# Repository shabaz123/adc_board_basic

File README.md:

# adc_board_basic
ADC board in the shape of a Pi Pico

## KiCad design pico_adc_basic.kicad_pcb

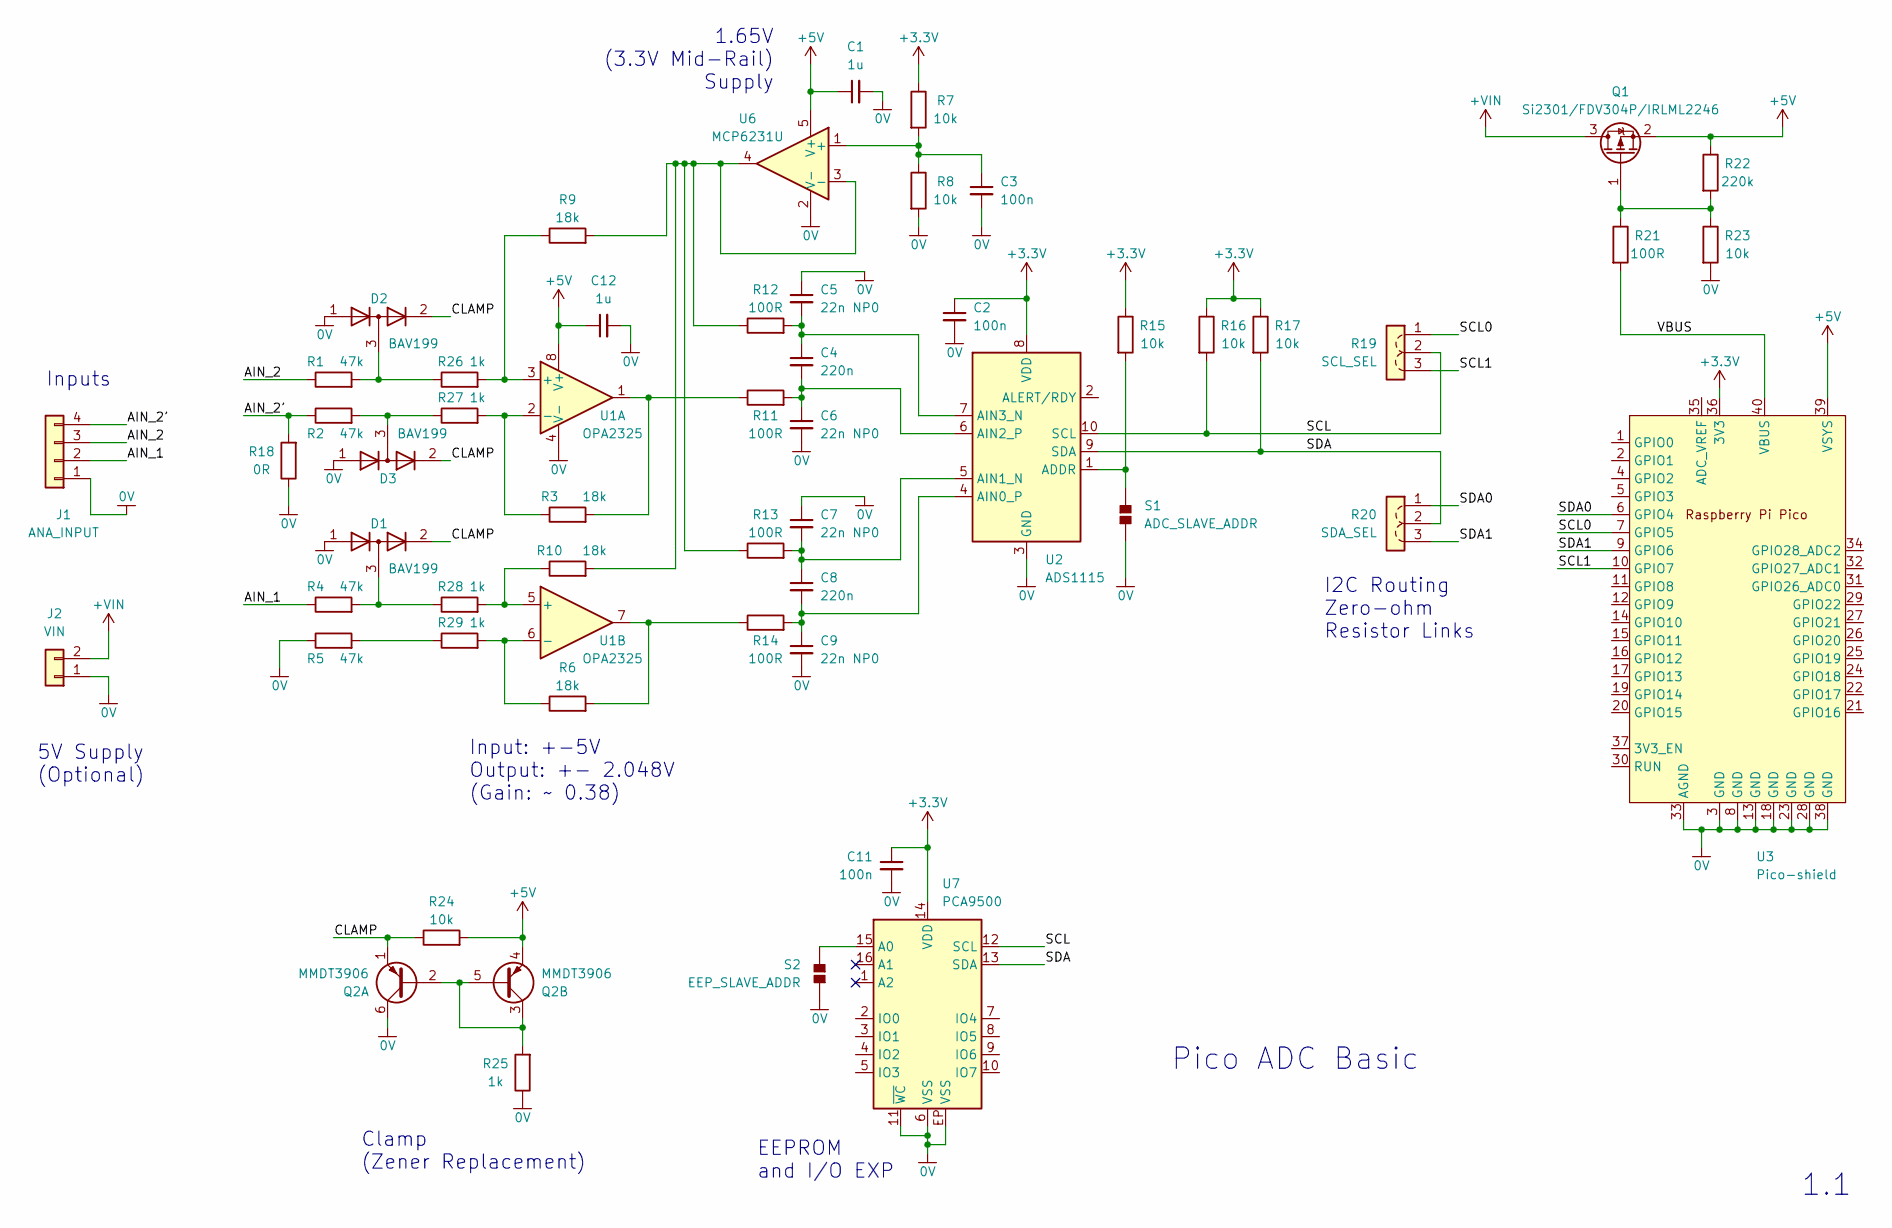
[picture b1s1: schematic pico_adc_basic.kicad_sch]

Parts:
C1, C12: 1u; C_0805_2012Metric_Pad1.18x1.45mm_HandSolder
C2, C3, C11: 100n; C_0603_1608Metric_Pad1.08x0.95mm_HandSolder
C4, C8: 220n; C_0603_1608Metric_Pad1.08x0.95mm_HandSolder
C5, C6, C7, C9: 22n NP0; C_0603_1608Metric_Pad1.08x0.95mm_HandSolder
D1, D2, D3: BAV199; SC70-3
J1: ANA_INPUT; PinHeader_1x04_P2.54mm_Vertical
J2: VIN; PinHeader_1x02_P2.54mm_Vertical
Q1: Si2301/FDV304P/IRLML2246; SOT-23_Handsoldering
Q2: MMDT3906; SC70-6
R1, R2, R4, R5: 47k; R_0603_1608Metric_Pad0.98x0.95mm_HandSolder
R3, R6, R9, R10: 18k; R_0603_1608Metric_Pad0.98x0.95mm_HandSolder
R7, R8, R15, R16, R17, R23, R24: 10k; R_0603_1608Metric_Pad0.98x0.95mm_HandSolder
R11, R12, R13, R14, R21: 100R; R_0603_1608Metric_Pad0.98x0.95mm_HandSolder
R18: 0R; R_0603_1608Metric_Pad0.98x0.95mm_HandSolder
R19: SCL_SEL; R_0805_option_3pads
R20: SDA_SEL; R_0805_option_3pads
R22: 220k; R_0603_1608Metric_Pad0.98x0.95mm_HandSolder
R25, R26, R27, R28, R29: 1k; R_0603_1608Metric_Pad0.98x0.95mm_HandSolder
S1: ADC_SLAVE_ADDR; short-option-small
S2: EEP_SLAVE_ADDR; short-option-small
U1: OPA2325; VSSOP-8-DGK-TI
U2: ADS1115; VSSOP-10-TI
U3: Pico-shield; pi-pico-shield
U6: MCP6231U; SC70-5-DCK-TI
U7: PCA9500; HVQFN16-SOT626-1-NXP

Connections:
0V: C1.2, C2.2, C3.2, C5.1, C6.2, C7.1, C9.2, C11.2, C12.2, D1.1 (A), D2.1 (A), D3.1 (A), J1.1, J2.1, Q2.6 (C1), R5.1, R8.2, R18.1, R23.2, R25.1, S1.1 (K), S2.1 (K), U1.4 (V-), U2.3 (GND), U3.3 (GND), U3.8 (GND), U3.13 (GND), U3.18 (GND), U3.23 (GND), U3.28 (GND), U3.33 (AGND), U3.38 (GND), U6.2 (V-), U7.6 (VSS), U7.11 (~WC), U7.EP (VSS)
+3.3V: C2.1, C11.1, R7.1, R15.1, R16.1, R17.1, U2.8 (VDD), U3.36 (3V3), U7.14 (VDD)
+5V: C1.1, C12.1, Q1.2 (S), Q2.4 (E2), R22.1, R24.2, U1.8 (V+), U3.39 (VSYS), U6.5 (V+)
+VIN: J2.2, Q1.3 (D)
/AIN_1: J1.2, R4.1
/AIN_2: J1.3, R1.1
/AIN_2': J1.4, R2.1, R18.2
/CLAMP: D1.2 (K), D2.2 (K), D3.2 (K), Q2.1 (E1), R24.1
/SCL: R16.2, R19.2, U2.10 (SCL), U7.12 (SCL)
/SCL0: R19.1, U3.7 (GPIO5)
/SCL1: R19.3, U3.10 (GPIO7)
/SDA: R17.2, R20.2, U2.9 (SDA), U7.13 (SDA)
/SDA0: R20.1, U3.6 (GPIO4)
/SDA1: R20.3, U3.9 (GPIO6)
/VBUS: R21.2, U3.40 (VBUS)
unnamed: D1.3 (KA), R4.2, R28.1
unnamed: D2.3 (KA), R1.2, R26.1
unnamed: D3.3 (KA), R2.2, R27.1
unnamed: Q1.1 (G), R21.1, R22.2, R23.1
unnamed: Q2.2 (B1), Q2.3 (C2), Q2.5 (B2), R25.2
unnamed: R3.2, R11.1, U1.1
unnamed: R6.2, R14.1, U1.7
unnamed: R5.2, R29.1
unnamed: R15.2, S1.2 (A), U2.1 (ADDR)
unnamed: S2.2 (A), U7.15 (A0)
unnamed: R9.1, R26.2, U1.3 (+)
unnamed: R3.1, R27.2, U1.2 (-)
unnamed: R10.1, R28.2, U1.5 (+)
unnamed: R6.1, R29.2, U1.6 (-)
unnamed: C8.2, C9.1, R14.2, U2.4 (AIN0_P)
unnamed: C7.2, C8.1, R13.2, U2.5 (AIN1_N)
unnamed: C4.2, C6.1, R11.2, U2.6 (AIN2_P)
unnamed: C4.1, C5.2, R12.2, U2.7 (AIN3_N)
unnamed: C3.1, R7.2, R8.1, U6.1 (+)
unnamed: R9.2, R10.2, R12.1, R13.1, U6.3 (-), U6.4

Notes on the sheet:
1.1
1.65V (3.3V Mid-Rail) Supply
Input: +-5V Output: +- 2.048V (Gain: ~ 0.38)
5V Supply (Optional)
Pico ADC Basic
EEPROM and I/O EXP
Inputs
Clamp (Zener Replacement)
I2C Routing Zero-ohm Resistor Links

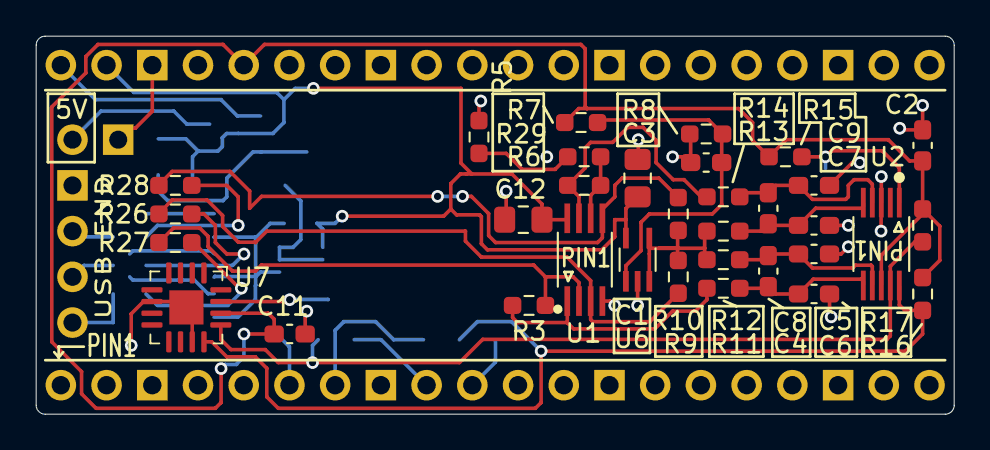
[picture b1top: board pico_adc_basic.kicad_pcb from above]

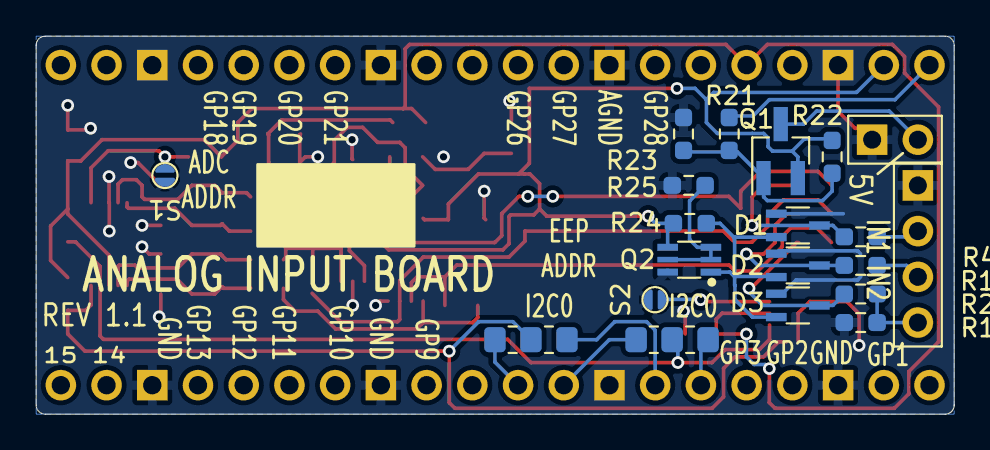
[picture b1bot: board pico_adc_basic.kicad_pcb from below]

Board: 2 copper layers, 51.0 x 21.0 mm, 54 parts (20 on the bottom side), 35 nets.
